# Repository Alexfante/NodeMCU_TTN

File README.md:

# NodeMCU_TTN
Kicad NodeMcu RFM95w TTN node with Battery charger

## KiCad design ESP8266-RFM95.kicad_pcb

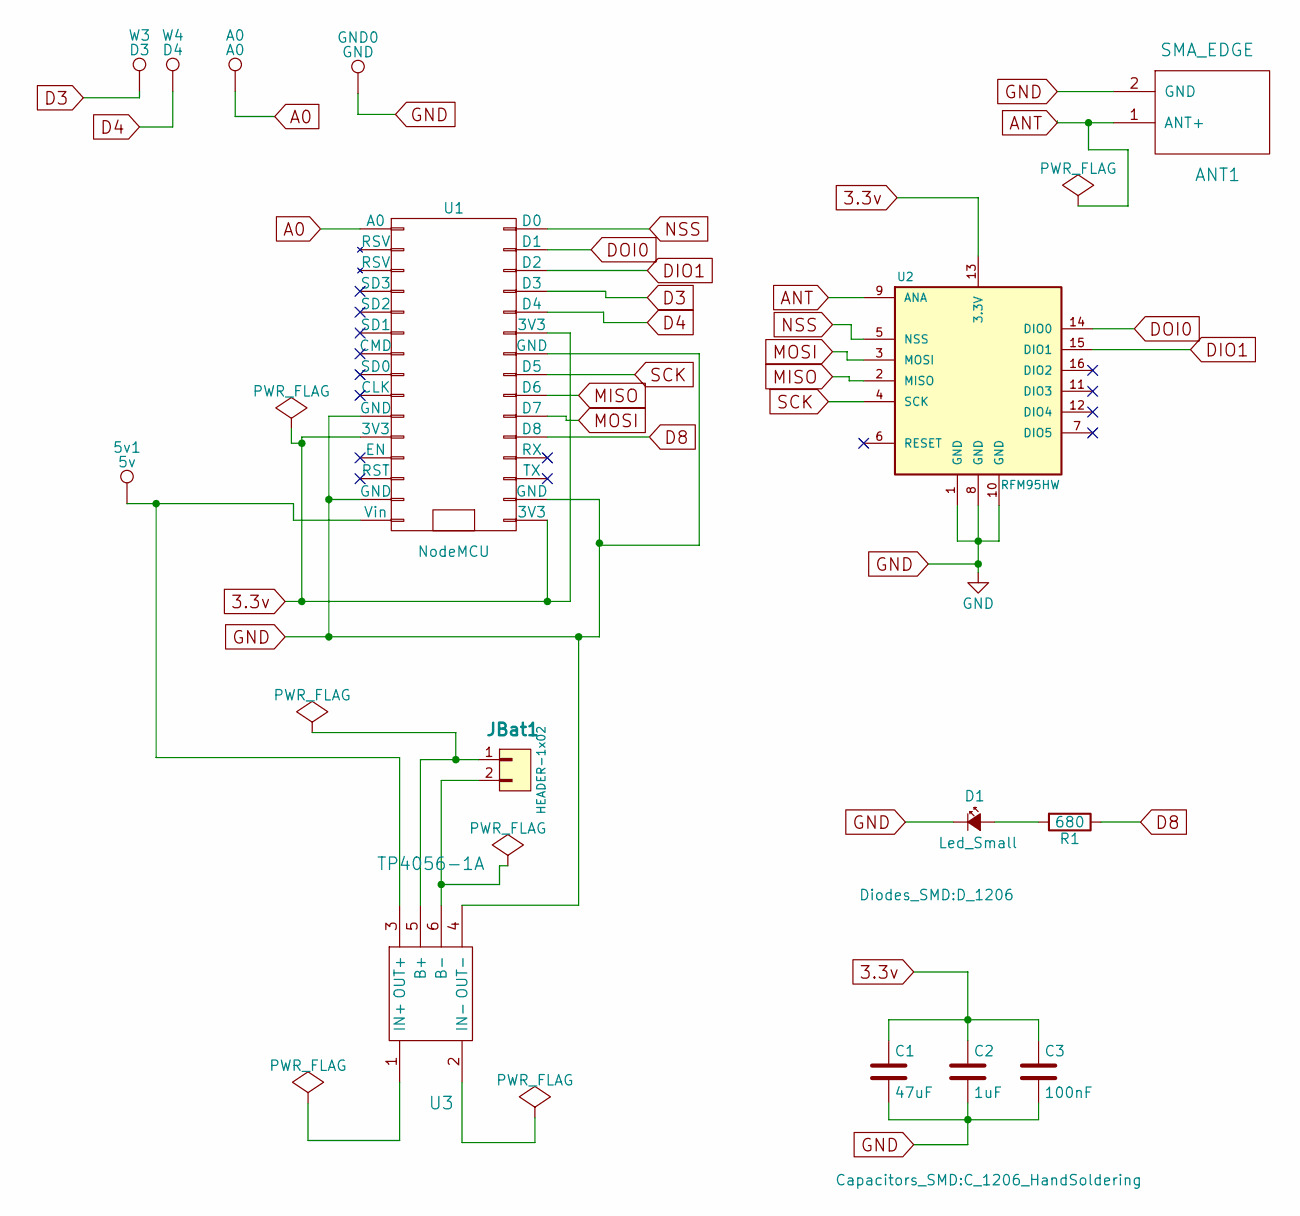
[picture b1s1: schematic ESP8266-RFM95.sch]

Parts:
5v1: 5v; SolderWirePad_single_0-8mmDrill
A0: A0; SolderWirePad_single_0-8mmDrill
ANT1: SMA_EDGE
C1: 47uF; C_1206_HandSoldering
C2: 1uF; C_1206_HandSoldering
C3: 100nF; C_1206_HandSoldering
D1: Led_Small; D_1206
GND0: GND; SolderWirePad_single_0-8mmDrill
JBat1: HEADER-1x02; JST_EH_S02B-EH_02x2.50mm_Angled
R1: 680; R_1206_HandSoldering
U1: NodeMCU; NodeMCU_Amica_R2
U2: RFM95HW; RFM92_95_96_98
U3: TP4056-1A; TP4056-18650
W3: D3; SolderWirePad_single_0-8mmDrill
W4: D4; SolderWirePad_single_0-8mmDrill

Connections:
3.3v: C1.1, C2.1, C3.1, U1.11 (3V3), U1.16 (3V3), U1.25 (3V3), U2.13 (3.3V)
A0: A0.1, U1.1 (A0)
ANT: ANT1.1 (ANT+), U2.9 (ANA)
D3: U1.27 (D3), W3.1
D4: U1.26 (D4), W4.1
D8: R1.1, U1.20 (D8)
DIO1: U1.28 (D2), U2.15 (DIO1)
DOI0: U1.29 (D1), U2.14 (DIO0)
GND: ANT1.2 (GND), C1.2, C2.2, C3.2, D1.1 (K), GND0.1, U1.10 (GND), U1.14 (GND), U1.17 (GND), U1.24 (GND), U2.1 (GND), U2.8 (GND), U2.10 (GND), U3.4 (OUT-)
MISO: U1.22 (D6), U2.2 (MISO)
MOSI: U1.21 (D7), U2.3 (MOSI)
NSS: U1.30 (D0), U2.5 (NSS)
unnamed: 5v1.1, U1.15 (Vin), U3.3 (OUT+)
unnamed: D1.2 (A), R1.2
unnamed: JBat1.1, U3.5 (B+)
unnamed: JBat1.2, U3.6 (B-)
SCK: U1.23 (D5), U2.4 (SCK)

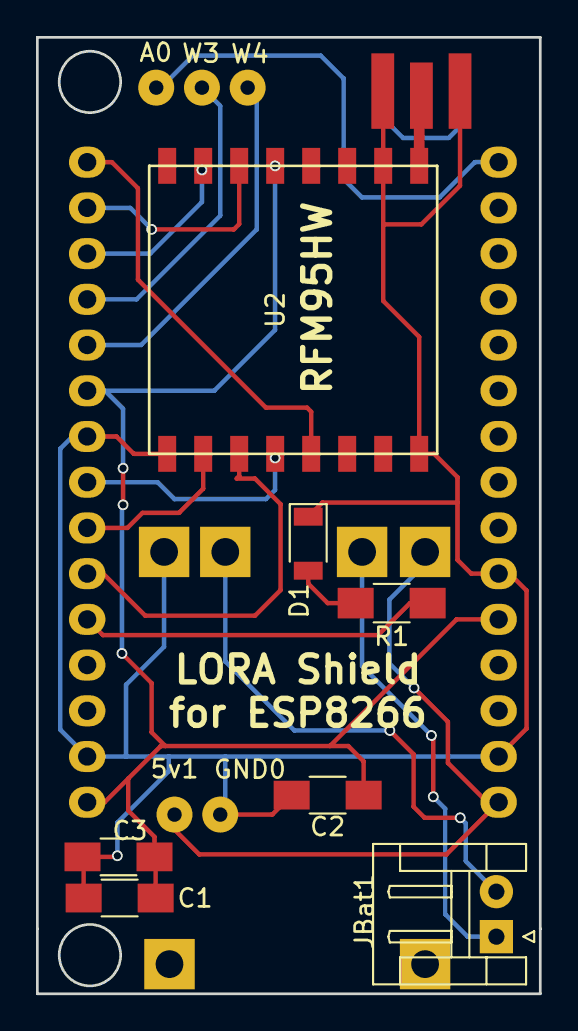
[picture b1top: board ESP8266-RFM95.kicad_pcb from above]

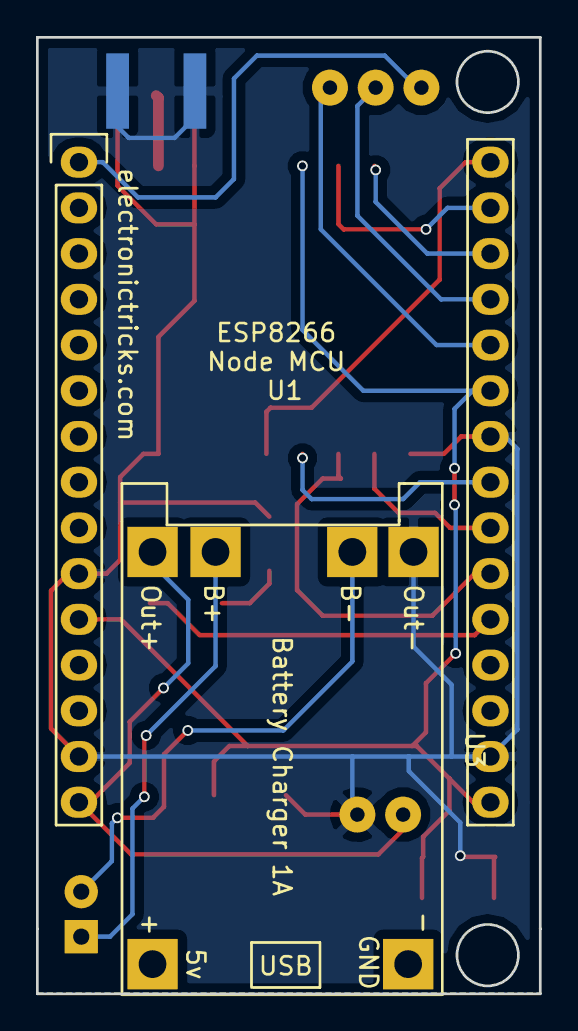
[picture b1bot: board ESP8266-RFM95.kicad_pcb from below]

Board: 2 copper layers, 27.9 x 53.1 mm, 15 parts (2 on the bottom side), 17 nets.
